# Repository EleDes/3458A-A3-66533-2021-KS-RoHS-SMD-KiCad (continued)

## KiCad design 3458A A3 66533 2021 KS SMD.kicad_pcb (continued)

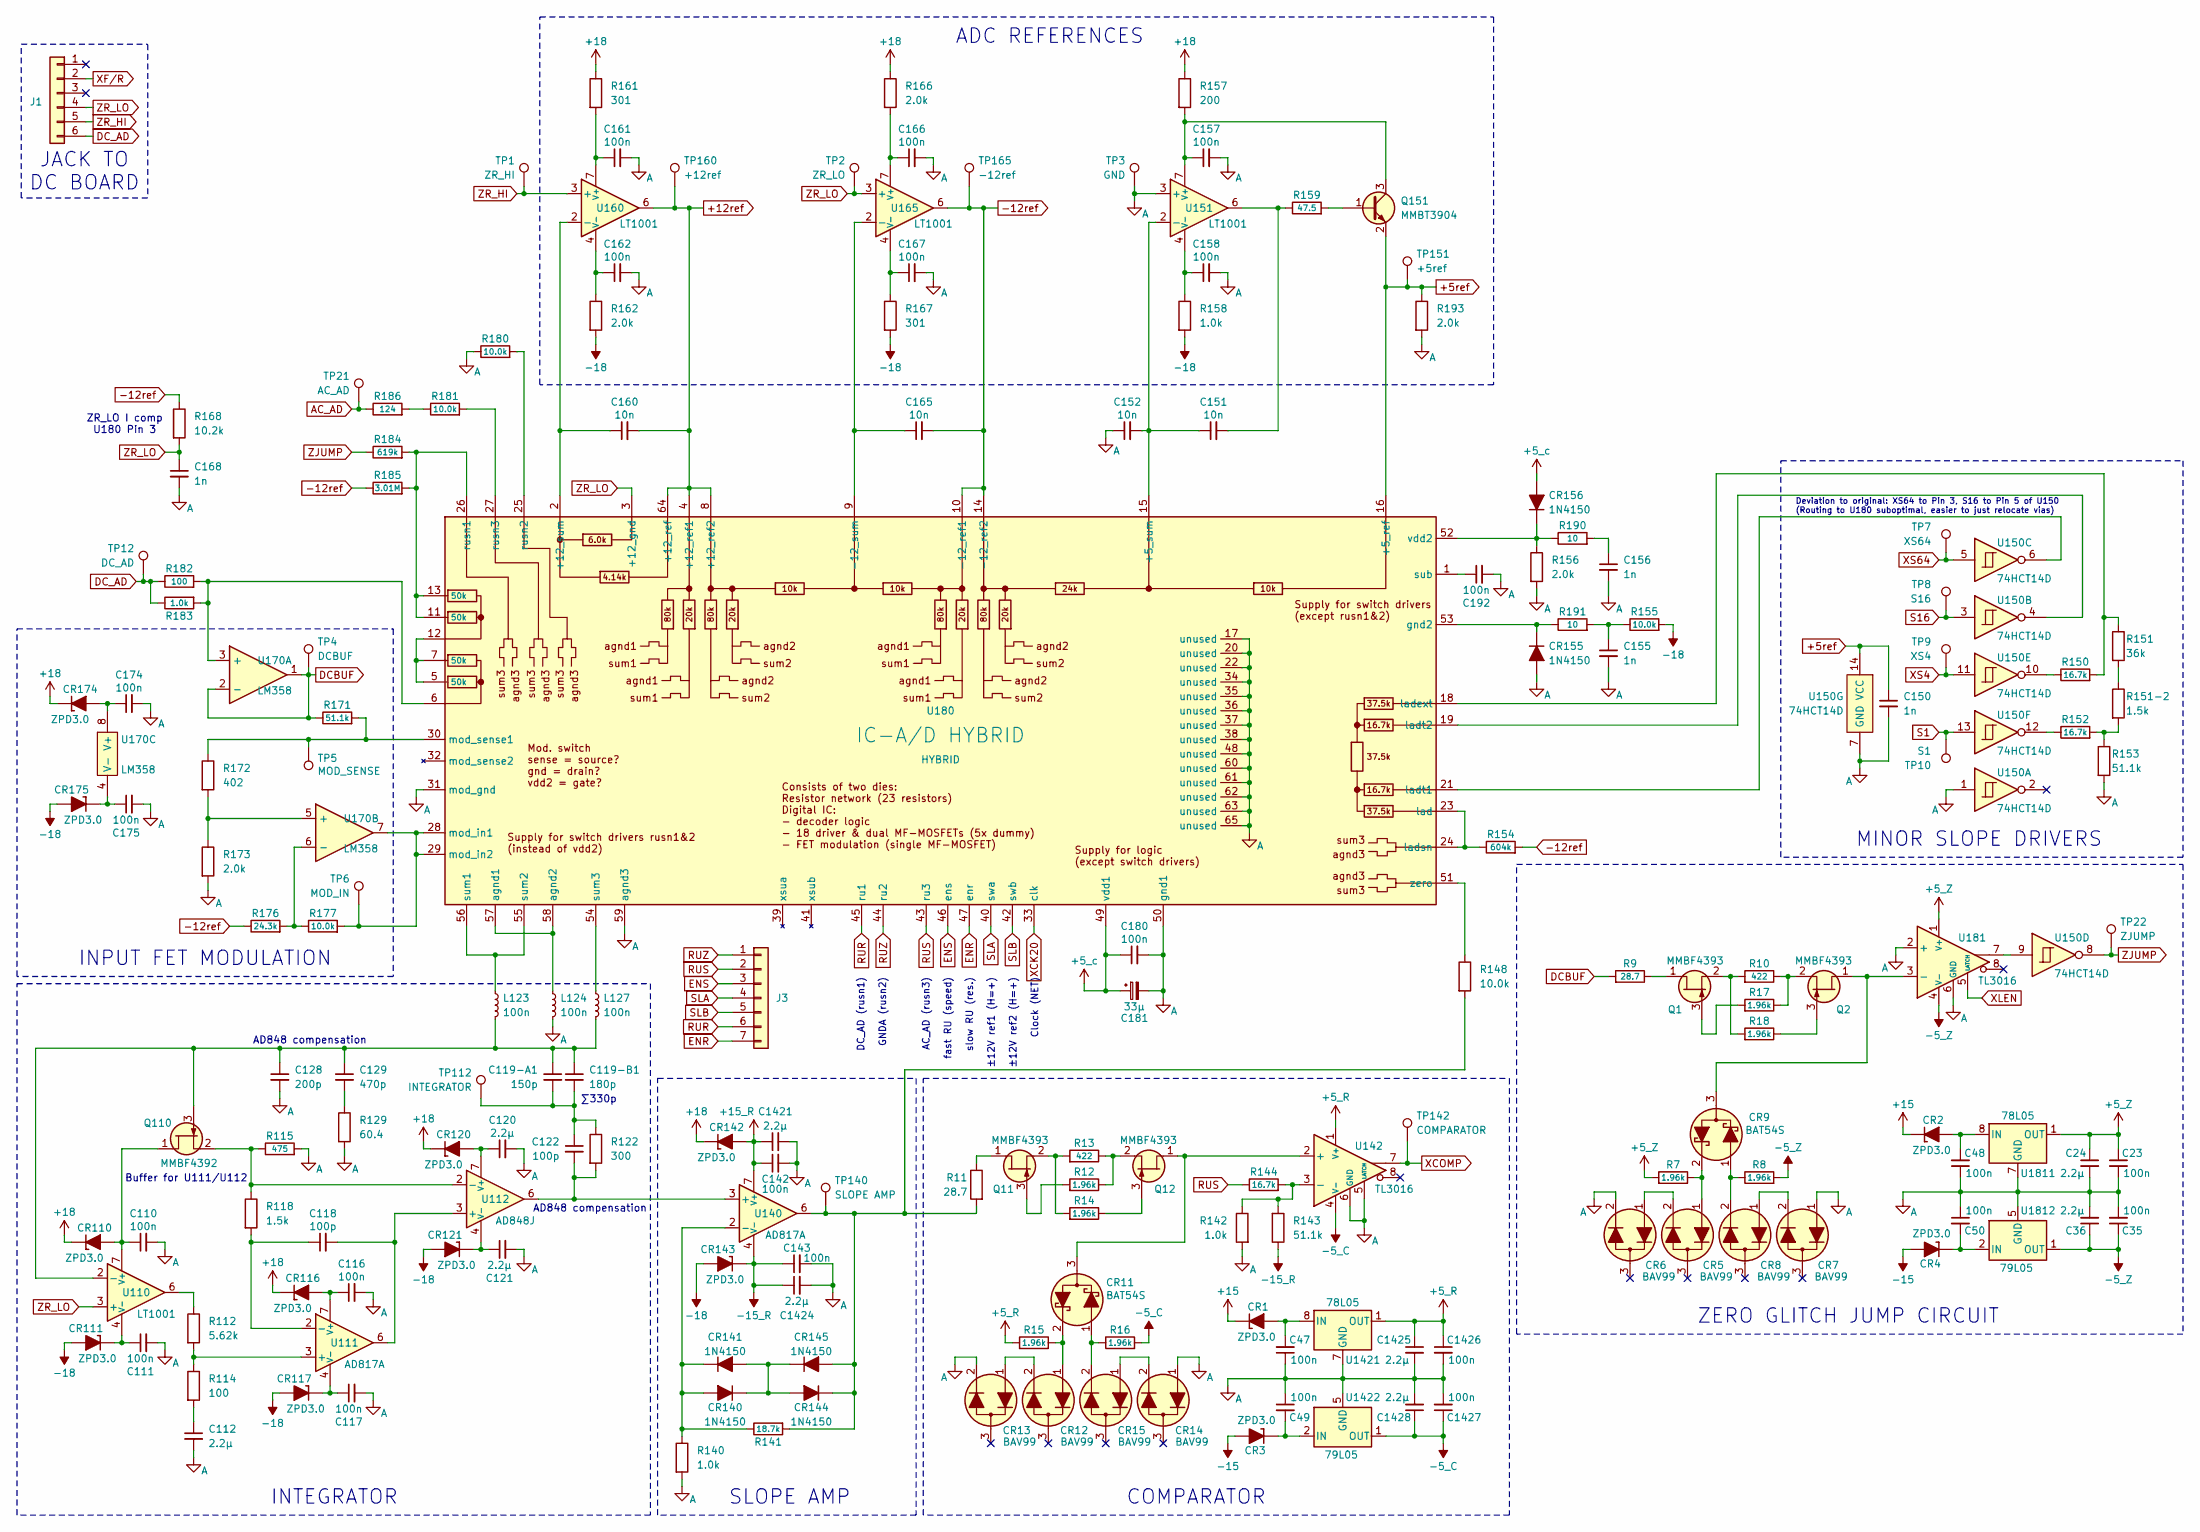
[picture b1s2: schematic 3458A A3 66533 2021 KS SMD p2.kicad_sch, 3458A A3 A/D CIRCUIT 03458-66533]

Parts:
C23, C35, C47, C48, C49, C50, C110, C111, C116, C117, C142, C143, C157, C158, C161, C162, C166, C167, C174, C175, C180, C192, C1426, C1427: 100n; C_0603_1608Metric
C24, C36, C112, C120, C121, C1421, C1424, C1425, C1428: 2.2µ; C_0805_2012Metric
C118, C122: 100p; C_0805_2012Metric
C119-A1: 150p; C_0805_2012Metric
C119-B1: 180p; C_0805_2012Metric
C128: 200p; C_0603_1608Metric
C129: 470p; C_0603_1608Metric
C150, C155, C156, C168: 1n; C_0603_1608Metric
C151, C152, C160, C165: 10n; C_0805_2012Metric
C181: 33µ; CP_EIA-3528-21_Kemet-B
CR1, CR2, CR3, CR4, CR110, CR111, CR116, CR117, CR120, CR121, CR142, CR143, CR174, CR175: ZPD3.0; D_SOD-123; Mfr. Part Number MMSZ5225B
CR5, CR6, CR7, CR8, CR12, CR13, CR14, CR15: BAV99; SOT-23W; Mfr. Part Number BAV99
CR9, CR11: BAT54S; SOT-23W; Mfr. Part Number BAT54S
CR140, CR141, CR144, CR145, CR155, CR156: 1N4150; D_SOD-123; Mfr. Part Number 1N4150W
J1: Conn_01x06; CONN_SDA-41815_06_BE_H_MOL; Mfr. Part Number 09-48-3064
J3: Conn_01x07; PinHeader_1x07_P2.54mm_Vertical
L123, L124, L127: 100n; L_0805_2012Metric
Q1, Q2, Q11, Q12: MMBF4393; SOT-23W; Mfr. Part Number MMBF4393
Q110: MMBF4392; SOT-23W; Mfr. Part Number MMBF4392
Q151: MMBT3904; SOT-23W; Mfr. Part Number MMBT3904
R7, R8, R12, R14, R15, R16, R17, R18: 1.96k; R_1206_3216Metric
R9, R11: 28.7; R_1206_3216Metric
R10, R13: 422; R_1206_3216Metric
R112: 5.62k; R_1206_3216Metric
R114, R182: 100; R_1206_3216Metric
R115: 475; R_1206_3216Metric
R118, R151-2: 1.5k; R_1206_3216Metric
R122: 300; R_1206_3216Metric
R129: 60.4; R_1206_3216Metric
R140, R142, R158, R183: 1.0k; R_1206_3216Metric
R141: 18.7k; R_1206_3216Metric
R143, R153, R171: 51.1k; R_1206_3216Metric
R144, R150, R152: 16.7k; R_1206_3216Metric
R148, R155, R177, R180: 10.0k; R_1206_3216Metric
R151: 36k; R_1206_3216Metric
R154: 604k; R_1206_3216Metric
R156, R162, R166, R173, R193: 2.0k; R_1206_3216Metric
R157: 200; R_1206_3216Metric
R159: 47.5; R_1206_3216Metric
R161, R167: 301; R_1206_3216Metric
R168: 10.2k; R_1206_3216Metric
R172: 402; R_1206_3216Metric
R176: 24.3k; R_1206_3216Metric
R181: 10.0k; R_1206_3216Metric; Mfr. Part Number TNPU120610K0BZ
R184: 619k; R_1206_3216Metric
R185: 3.01M; R_1206_3216Metric
R186: 124; R_1206_3216Metric
R190, R191: 10; R_1206_3216Metric
TP1: ZR_HI; TestPoint_THTPad_2.0x2.0mm_Drill1.0mm; Mfr. Part Number 16-06-0034
TP2: ZR_LO; TestPoint_THTPad_2.0x2.0mm_Drill1.0mm; Mfr. Part Number 16-06-0034
TP3: GND; TestPoint_THTPad_2.0x2.0mm_Drill1.0mm; Mfr. Part Number 16-06-0034
TP4: DCBUF; TestPoint_THTPad_2.0x2.0mm_Drill1.0mm; Mfr. Part Number 16-06-0034
TP5: MOD_SENSE; TestPoint_THTPad_2.0x2.0mm_Drill1.0mm; Mfr. Part Number 16-06-0034
TP6: MOD_IN; TestPoint_THTPad_2.0x2.0mm_Drill1.0mm; Mfr. Part Number 16-06-0034
TP7: XS64; TestPoint_THTPad_2.0x2.0mm_Drill1.0mm; Mfr. Part Number 16-06-0034
TP8: S16; TestPoint_THTPad_2.0x2.0mm_Drill1.0mm; Mfr. Part Number 16-06-0034
TP9: XS4; TestPoint_THTPad_2.0x2.0mm_Drill1.0mm; Mfr. Part Number 16-06-0034
TP10: S1; TestPoint_THTPad_2.0x2.0mm_Drill1.0mm; Mfr. Part Number 16-06-0034
TP12: DC_AD; TestPoint_THTPad_2.0x2.0mm_Drill1.0mm; Mfr. Part Number 16-06-0034
TP21: AC_AD; TestPoint_THTPad_2.0x2.0mm_Drill1.0mm; Mfr. Part Number 16-06-0034
TP22: ZJUMP; TestPoint_THTPad_2.0x2.0mm_Drill1.0mm; Mfr. Part Number 16-06-0034
TP112: INTEGRATOR; TestPoint_THTPad_2.0x2.0mm_Drill1.0mm; Mfr. Part Number 16-06-0034
TP140: SLOPE AMP; TestPoint_THTPad_2.0x2.0mm_Drill1.0mm; Mfr. Part Number 16-06-0034
TP142: COMPARATOR; TestPoint_THTPad_2.0x2.0mm_Drill1.0mm; Mfr. Part Number 16-06-0034
TP151: +5ref; TestPoint_THTPad_2.0x2.0mm_Drill1.0mm; Mfr. Part Number 16-06-0034
TP160: +12ref; TestPoint_THTPad_2.0x2.0mm_Drill1.0mm; Mfr. Part Number 16-06-0034
TP165: -12ref; TestPoint_THTPad_2.0x2.0mm_Drill1.0mm; Mfr. Part Number 16-06-0034
U110, U151, U160, U165: LT1001; SOIC-8_3.9x4.9mm_P1.27mm; Mfr. Part Number LT1001CS8
U111, U140: AD817A; SOIC-8_3.9x4.9mm_P1.27mm; Mfr. Part Number AD817AR
U112: AD848J; SOIC-8_3.9x4.9mm_P1.27mm; Mfr. Part Number AD848JR
U142, U181: TL3016; SOIC-8_3.9x4.9mm_P1.27mm; Mfr. Part Number TL3016
U150: 74HCT14D; SOIC-14_3.9x8.7mm_P1.27mm; Mfr. Part Number 74HCT14D
U170: LM358; SOIC-8_3.9x4.9mm_P1.27mm; Mfr. Part Number LM358
U180: HYBRID; U180_PGA-65; Mfr. Part Number 1SJ8-0108
U1421, U1811: 78L05; SOIC-8_3.9x4.9mm_P1.27mm; Mfr. Part Number MC78L05A
U1422, U1812: 79L05; SOIC-8_3.9x4.9mm_P1.27mm; Mfr. Part Number 79L05A

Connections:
+5_R: C1425.1, C1426.1, R15.2, U142.1 (V+), U1421.1 (OUT); also elsewhere on the board
+5_Z: C23.1, C24.1, R7.2, U181.1 (V+), U1811.1 (OUT); also elsewhere on the board
+5_c: C180.1, C181.1, CR156.2 (A), U180.49 (vdd1); also elsewhere on the board
+5ref: C150.1, Q151.2 (E), R193.1, TP151.1, U150.14 (VCC), U180.16 (+5_ref); also elsewhere on the board
+12ref: C160.2, TP160.1, U160.6, U180.4 (+12_ref1), U180.8 (+12_ref2), U180.64 (+12_ref); also elsewhere on the board
+15: CR1.1 (K), CR2.1 (K); also elsewhere on the board
+15_R: C142.1, C1421.1, CR142.2 (A), U140.7 (V+)
+18: CR110.1 (K), CR116.1 (K), CR120.1 (K), CR142.1 (K), CR174.1 (K), R157.1, R161.1, R166.1; also elsewhere on the board
-5_C: C1427.1, C1428.1, R16.2, U142.4 (V-), U1422.1 (OUT); also elsewhere on the board
-5_Z: C35.1, C36.1, R8.2, U181.4 (V-), U1812.1 (OUT); also elsewhere on the board
-12ref: C165.2, R154.2, R168.1, R176.1, R185.1, TP165.1, U165.6, U180.10 (-12_ref1), U180.14 (-12_ref2); also elsewhere on the board
-15: CR3.2 (A), CR4.2 (A); also elsewhere on the board
-15_R: C143.1, C1424.1, CR143.1 (K), R143.1, U140.4 (V-)
-18: CR111.2 (A), CR117.2 (A), CR121.2 (A), CR143.2 (A), CR175.2 (A), R155.2, R158.2, R162.2, R167.2; also elsewhere on the board
AC_AD: R186.1, TP21.1; also elsewhere on the board
DCBUF: R9.2, R171.1, TP4.1, U170.1, U170.2 (-)
DC_AD: J1.6, R182.1, R183.1, TP12.1
ENR: J3.7, U180.47 (enr); also elsewhere on the board
ENS: J3.3, U180.46 (ens); also elsewhere on the board
unnamed: C112.1, R114.2
unnamed: C119-A1.2, C119-B1.2, C122.1, R122.1, TP112.1
unnamed: C129.2, R129.1
unnamed: C151.2, R159.1, U151.6
unnamed: C155.1, R155.1, R191.2
unnamed: C156.1, R190.2
unnamed: C47.2, CR1.2 (A), U1421.8 (IN)
unnamed: C48.2, CR2.2 (A), U1811.8 (IN)
unnamed: C49.2, CR3.1 (K), U1422.2 (IN), U1422.3 (IN), U1422.6 (IN), U1422.7 (IN)
unnamed: C50.2, CR4.1 (K), U1812.2 (IN), U1812.3 (IN), U1812.6 (IN), U1812.7 (IN)
unnamed: CR5.1 (A), CR9.2 (K), R7.1
unnamed: CR5.2 (K), CR6.1 (A)
unnamed: CR7.2 (K), CR8.1 (A)
unnamed: CR8.2 (K), CR9.1 (A), R8.1
unnamed: CR9.3 (C), Q2.1 (D), U181.3 (-)
unnamed: CR11.1 (A), CR15.2 (K), R16.1
unnamed: CR11.3 (C), Q12.1 (D), U142.2 (+)
unnamed: CR11.2 (K), CR12.1 (A), R15.1
unnamed: CR12.2 (K), CR13.1 (A)
unnamed: CR14.2 (K), CR15.1 (A)
unnamed: C110.1, CR110.2 (A), Q110.1 (D), U110.7 (V+)
unnamed: C111.1, CR111.1 (K), U110.4 (V-)
unnamed: C116.1, CR116.2 (A), U111.7 (V+)
unnamed: C117.1, CR117.1 (K), U111.4 (V-)
unnamed: C120.1, CR120.2 (A), U112.7 (V+)
unnamed: C121.1, CR121.1 (K), U112.4 (V-)
unnamed: CR140.2 (A), CR141.1 (K), R140.1, R141.1, U140.2 (-)
unnamed: CR140.1 (K), CR141.2 (A), CR144.2 (A), CR145.1 (K)
unnamed: CR144.1 (K), CR145.2 (A), R11.2, R141.2, R148.2, TP140.1, U140.6
unnamed: CR155.1 (K), R191.1, U180.53 (gnd2)
unnamed: CR156.1 (K), R156.1, R190.1, U180.52 (vdd2)
unnamed 129: C174.1, CR174.2 (A), U170.8 (V+); also elsewhere on the board
unnamed 130: C175.1, CR175.1 (K), U170.4 (V-); also elsewhere on the board
unnamed: Q1.1 (D), R9.1
unnamed: Q1.3 (G), R17.2
unnamed: Q1.2 (S), R10.2, R18.2
unnamed: Q2.3 (G), R18.1
unnamed: Q2.2 (S), R10.1, R17.1
unnamed: Q11.1 (D), R11.1
unnamed: Q11.3 (G), R12.2
unnamed: Q11.2 (S), R13.2, R14.2
unnamed: Q12.3 (G), R14.1
unnamed: Q12.2 (S), R12.1, R13.1
unnamed: C119-A1.1, C119-B1.1, C128.1, C129.1, L123.2, L127.2, Q110.3 (G), U110.2 (-)
unnamed: Q110.2 (S), R115.1, R118.1, U112.2 (-)
unnamed: Q151.1 (B), R159.2
unnamed: C157.1, Q151.3 (C), R157.2, U151.7 (V+)
unnamed: R112.1, U110.6
unnamed: R150.1, U150.10
unnamed: R151.2, R151-2.1
unnamed: R151-2.2, R152.2, R153.1
unnamed: R152.1, U150.12
unnamed: R181.1, R186.2
unnamed: R112.2, R114.1, U111.3 (+)
unnamed: C118.1, R118.2, U111.2 (-)
unnamed: C118.2, U111.6, U112.3 (+)
unnamed: C122.2, R122.2, U112.6, U140.3 (+)
unnamed: R142.1, R143.2, R144.2, U142.3 (-)
unnamed: U150.9, U181.7
unnamed: C151.1, C152.2, U151.2 (-), U180.15 (+5_sum)
unnamed: C158.1, R158.1, U151.4 (V-)
unnamed: C160.1, U160.2 (-), U180.2 (+12_sum)
unnamed: C161.1, R161.2, U160.7 (V+)
unnamed: C162.1, R162.1, U160.4 (V-)
unnamed: C165.1, U165.2 (-), U180.9 (-12_sum)
unnamed: C166.1, R166.2, U165.7 (V+)
unnamed: C167.1, R167.1, U165.4 (V-)
unnamed: R182.2, R183.2, U170.3 (+), U180.6
unnamed: R172.2, R173.1, U170.5 (+)
unnamed: R176.2, R177.1, U170.6 (-)
unnamed: U180.5 (50k), U180.7 (50k), U180.12
unnamed: L124.1, U180.57 (agnd1), U180.58 (agnd2)
unnamed: R154.1, U180.23 (lad), U180.24 (ladsn)
unnamed: R150.2, R151.1, U180.18 (ladext)
unnamed: U150.6, U180.21 (ladt1)
unnamed: U150.4, U180.19 (ladt2)
unnamed: R177.2, TP6.1, U170.7, U180.28 (mod_in1), U180.29 (mod_in2)
unnamed: R171.2, R172.1, TP5.1, U180.30 (mod_sense1)
unnamed: R184.2, R185.2, U180.11 (50k), U180.13 (50k), U180.26 (rusn1)
unnamed: R180.2, U180.25 (rusn2)
unnamed: R181.2, U180.27 (rusn3)
unnamed: C192.1, U180.1 (sub)
unnamed: L123.1, U180.55 (sum2), U180.56 (sum1)
unnamed: L127.1, U180.54 (sum3)
unnamed: R148.1, U180.51 (zero)
PS_SENSE: C23.2, C24.2, C35.2, C36.2, C47.1, C48.1, C49.1, C50.1, C110.2, C111.2, C112.2, C116.2, C117.2, C120.2, C121.2, C128.2, C142.2, C143.2, C150.2, C152.1, C155.2, C156.2, C157.2, C158.2, C161.2, C162.2, C166.2, C167.2, C168.2, C174.2, C175.2, C180.2, C181.2, C192.2, C1421.2, C1424.2, C1425.2, C1426.2, C1427.2, C1428.2, CR6.2 (K), CR7.1 (A), CR13.2 (K), CR14.1 (A), CR155.2 (A), L124.2, R115.2, R129.2, R140.2, R142.2, R153.2, R156.2, R173.2, R180.1, R193.2, TP3.1, U142.5 (LATCH), U142.6 (GND), U150.1, U150.7 (GND), U151.3 (+), U180.17 (unused), U180.20 (unused), U180.22 (unused), U180.31 (mod_gnd), U180.34 (unused), U180.35 (unused), U180.36 (unused), U180.37 (unused), U180.38 (unused), U180.48 (unused), U180.50 (gnd1), U180.59 (agnd3), U180.60 (unused), U180.61 (unused), U180.62 (unused), U180.63 (unused), U180.65 (unused), U181.2 (+), U181.6 (GND), U1421.2 (GND), U1421.3 (GND), U1421.6 (GND), U1421.7 (GND), U1422.5 (GND), U1811.2 (GND), U1811.3 (GND), U1811.6 (GND), U1811.7 (GND), U1812.5 (GND); also elsewhere on the board
RUR: J3.6, U180.45 (ru1); also elsewhere on the board
RUS: J3.2, R144.1, U180.43 (ru3); also elsewhere on the board
RUZ: J3.1, U180.44 (ru2); also elsewhere on the board
S1: TP10.1, U150.13; also elsewhere on the board
S16: TP8.1, U150.3; also elsewhere on the board
SLA: J3.4, U180.40 (swa); also elsewhere on the board
SLB: J3.5, U180.42 (swb); also elsewhere on the board
XCK20: U180.33 (clk); also elsewhere on the board
XCOMP: TP142.1, U142.7; also elsewhere on the board
XF/R: J1.2; also elsewhere on the board
XLEN: U181.5 (LATCH); also elsewhere on the board
XS4: TP9.1, U150.11; also elsewhere on the board
XS64: TP7.1, U150.5; also elsewhere on the board
ZJUMP: R184.1, TP22.1, U150.8
ZR_HI: J1.5, TP1.1, U160.3 (+)
ZR_LO: C168.1, J1.4, R168.2, TP2.1, U110.3 (+), U165.3 (+), U180.3 (+12_gnd)

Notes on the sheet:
ZR_LO I comp U180 Pin 3
JACK TO DC BOARD
INPUT FET MODULATION
AD848 compensation
ZERO GLITCH JUMP CIRCUIT
MINOR SLOPE DRIVERS
Deviation to original: XS64 to Pin 3, S16 to Pin 5 of U150 (Routing to U180 suboptimal, easier to just relocate vias)
ADC REFERENCES
INTEGRATOR
Buffer for U111/U112
∑330p
SLOPE AMP
DC_AD (rusn1) GNDA (rusn2) AC_AD (rusn3) fast RU (speed) slow RU (res.) ±12V ref1 (H=+) ±12V ref2 (H=+) Clock (NET)
COMPARATOR

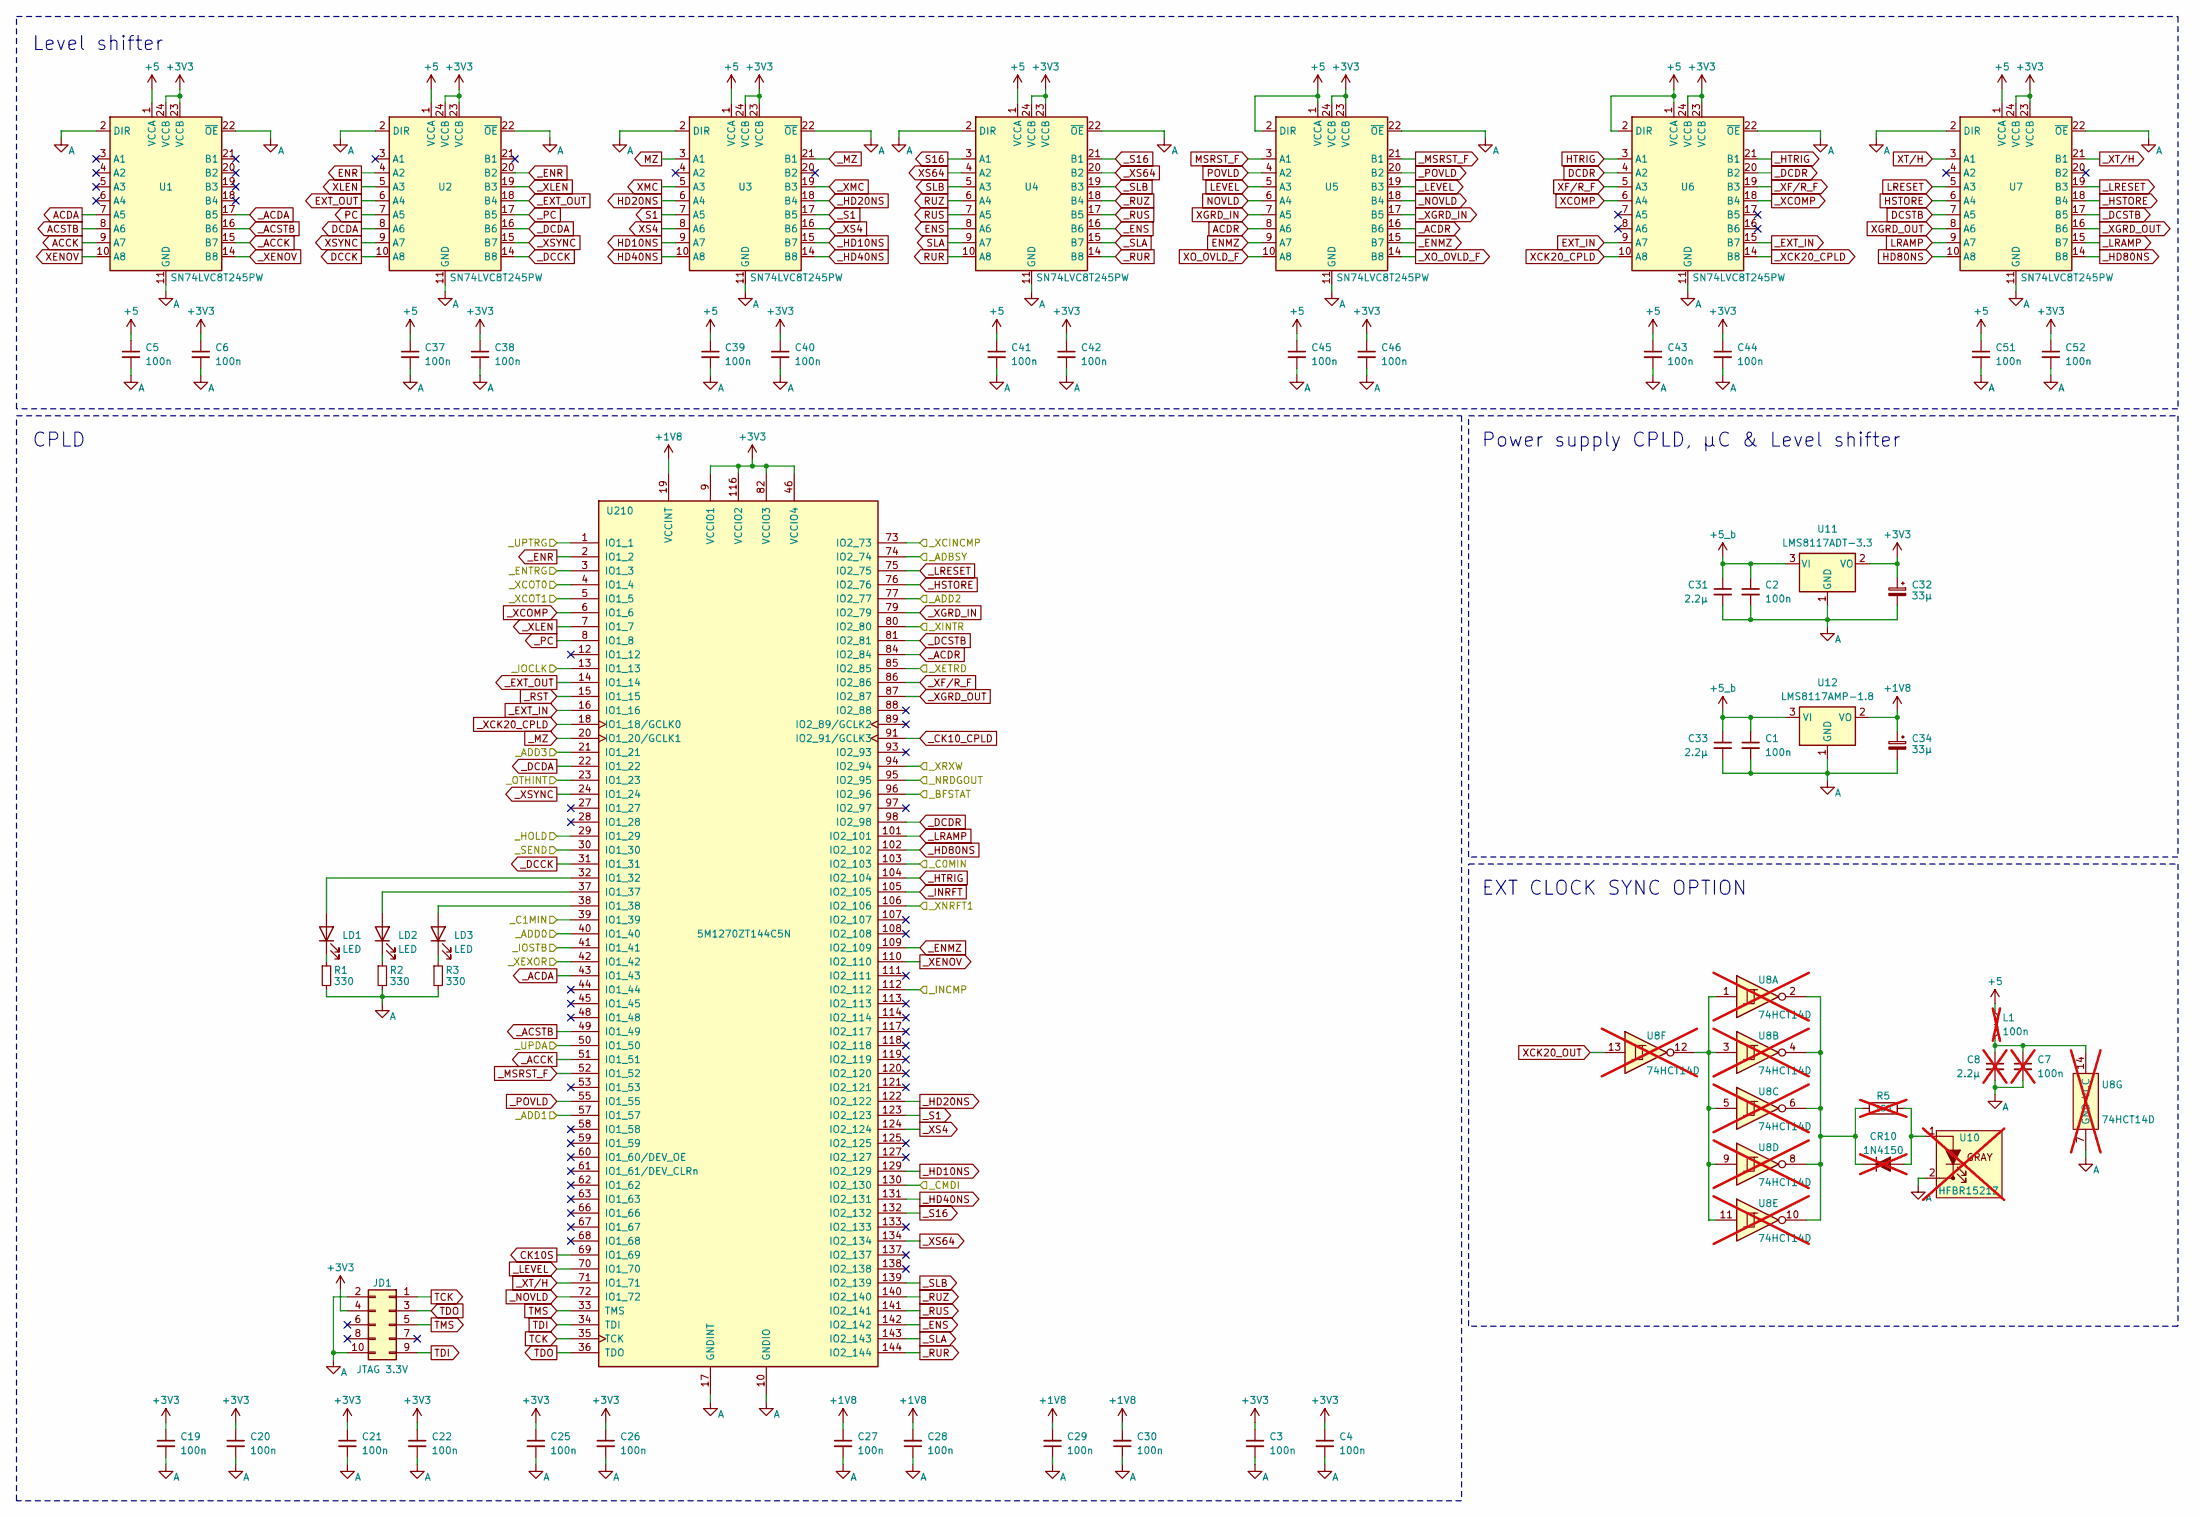
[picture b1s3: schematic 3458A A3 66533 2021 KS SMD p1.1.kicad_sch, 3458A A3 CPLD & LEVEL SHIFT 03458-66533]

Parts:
C1, C2, C3, C4, C5, C6, C19, C20, C21, C22, C25, C26, C28, C29, C30, C37, C38, C39, C40, C41, C42, C43, C44, C46, C51, C52: 100n; C_0603_1608Metric
C7: 100n; C_0603_1608Metric; not fitted
C8: 2.2µ; C_0805_2012Metric; not fitted
C27, C45: 100n; C_0805_2012Metric
C31, C33: 2.2µ; C_0805_2012Metric
C32, C34: 33µ; CP_EIA-3528-21_Kemet-B
CR10: 1N4150; D_SOD-123; Mfr. Part Number 1N4150W; not fitted
JD1: JTAG 3.3V; PinHeader_2x05_P2.54mm_Vertical
L1: 100n; L_0603_1608Metric; not fitted
LD1, LD2, LD3: LED; LED_0603_1608Metric
R1, R2, R3: 330; R_0603_1608Metric
R5: 150; R_1206_3216Metric; not fitted
U1, U2, U3, U4, U5, U6, U7: SN74LVC8T245PW; TSSOP-24_4.4x7.8mm_P0.65mm; Mfr. Part Number SN74LVC8T245PW
U8: 74HCT14D; SOIC-14_3.9x8.7mm_P1.27mm; Mfr. Part Number 74HCT14D; not fitted
U10: HFBR1521Z; HFBR-1521Z Fiber Optic; Mfr. Part Number HFBR1521Z; not fitted
U11: LMS8117ADT-3.3; TO-252-2; Mfr. Part Number LMS8117ADT-3.3
U12: LMS8117AMP-1.8; SOT-223-3_TabPin2; Mfr. Part Number LMS8117AMP-1.8
U210: 5M1270ZT144C5N; LQFP-144_20x20mm_P0.5mm; Mfr. Part Number 5M1270ZT144C5N

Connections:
+1V8: C27.1, C28.2, C29.2, C30.2, C34.1, U12.2 (VO), U210.19 (VCCINT), U210.56 (VCCINT), U210.90 (VCCINT), U210.126 (VCCINT); also elsewhere on the board
+3V3: C3.1, C4.1, C6.1, C19.1, C20.1, C21.1, C22.1, C25.1, C26.1, C32.1, C38.1, C40.1, C42.1, C44.1, C46.1, C52.1, JD1.4, U1.23 (VCCB), U1.24 (VCCB), U2.23 (VCCB), U2.24 (VCCB), U3.23 (VCCB), U3.24 (VCCB), U4.23 (VCCB), U4.24 (VCCB), U5.23 (VCCB), U5.24 (VCCB), U6.23 (VCCB), U6.24 (VCCB), U7.23 (VCCB), U7.24 (VCCB), U11.2 (VO), U210.9 (VCCIO1), U210.25 (VCCIO1), U210.46 (VCCIO4), U210.64 (VCCIO4), U210.82 (VCCIO3), U210.100 (VCCIO3), U210.116 (VCCIO2), U210.136 (VCCIO2); also elsewhere on the board
+5: C5.1, C37.1, C39.1, C41.1, C43.1, C45.1, C51.1, L1.1, U1.1 (VCCA), U2.1 (VCCA), U3.1 (VCCA), U4.1 (VCCA), U5.1 (VCCA), U5.2 (DIR), U6.1 (VCCA), U6.2 (DIR), U7.1 (VCCA); also elsewhere on the board
+5_b: C1.1, C2.1, C31.1, C33.1, U11.3 (VI), U12.3 (VI); also elsewhere on the board
/A3 IN-GRD CTL & INTERPOLATOR/CPLD & LEVEL SHIFT (Seite 2)/_ADBSY: U210.74 (IO2_74); also elsewhere on the board
/A3 IN-GRD CTL & INTERPOLATOR/CPLD & LEVEL SHIFT (Seite 2)/_ADD0: U210.40 (IO1_40); also elsewhere on the board
/A3 IN-GRD CTL & INTERPOLATOR/CPLD & LEVEL SHIFT (Seite 2)/_ADD1: U210.57 (IO1_57); also elsewhere on the board
/A3 IN-GRD CTL & INTERPOLATOR/CPLD & LEVEL SHIFT (Seite 2)/_ADD2: U210.77 (IO2_77); also elsewhere on the board
/A3 IN-GRD CTL & INTERPOLATOR/CPLD & LEVEL SHIFT (Seite 2)/_ADD3: U210.21 (IO1_21); also elsewhere on the board
/A3 IN-GRD CTL & INTERPOLATOR/CPLD & LEVEL SHIFT (Seite 2)/_BFSTAT: U210.96 (IO2_96); also elsewhere on the board
/A3 IN-GRD CTL & INTERPOLATOR/CPLD & LEVEL SHIFT (Seite 2)/_C0MIN: U210.103 (IO2_103); also elsewhere on the board
/A3 IN-GRD CTL & INTERPOLATOR/CPLD & LEVEL SHIFT (Seite 2)/_C1MIN: U210.39 (IO1_39); also elsewhere on the board
/A3 IN-GRD CTL & INTERPOLATOR/CPLD & LEVEL SHIFT (Seite 2)/_CMDI: U210.130 (IO2_130); also elsewhere on the board
/A3 IN-GRD CTL & INTERPOLATOR/CPLD & LEVEL SHIFT (Seite 2)/_ENTRG: U210.3 (IO1_3); also elsewhere on the board
/A3 IN-GRD CTL & INTERPOLATOR/CPLD & LEVEL SHIFT (Seite 2)/_HOLD: U210.29 (IO1_29); also elsewhere on the board
/A3 IN-GRD CTL & INTERPOLATOR/CPLD & LEVEL SHIFT (Seite 2)/_INCMP: U210.73 (IO2_73), U210.112 (IO2_112); also elsewhere on the board
/A3 IN-GRD CTL & INTERPOLATOR/CPLD & LEVEL SHIFT (Seite 2)/_IOCLK: U210.13 (IO1_13); also elsewhere on the board
/A3 IN-GRD CTL & INTERPOLATOR/CPLD & LEVEL SHIFT (Seite 2)/_IOSTB: U210.41 (IO1_41); also elsewhere on the board
/A3 IN-GRD CTL & INTERPOLATOR/CPLD & LEVEL SHIFT (Seite 2)/_NRDGOUT: U210.95 (IO2_95); also elsewhere on the board
/A3 IN-GRD CTL & INTERPOLATOR/CPLD & LEVEL SHIFT (Seite 2)/_OTHINT: U210.23 (IO1_23); also elsewhere on the board
/A3 IN-GRD CTL & INTERPOLATOR/CPLD & LEVEL SHIFT (Seite 2)/_SEND: U210.30 (IO1_30); also elsewhere on the board
/A3 IN-GRD CTL & INTERPOLATOR/CPLD & LEVEL SHIFT (Seite 2)/_UPDA: U210.50 (IO1_50); also elsewhere on the board
/A3 IN-GRD CTL & INTERPOLATOR/CPLD & LEVEL SHIFT (Seite 2)/_UPTRG: U210.1 (IO1_1); also elsewhere on the board
/A3 IN-GRD CTL & INTERPOLATOR/CPLD & LEVEL SHIFT (Seite 2)/_XETRD: U210.85 (IO2_85); also elsewhere on the board
/A3 IN-GRD CTL & INTERPOLATOR/CPLD & LEVEL SHIFT (Seite 2)/_XEXOR: U210.42 (IO1_42); also elsewhere on the board
/A3 IN-GRD CTL & INTERPOLATOR/CPLD & LEVEL SHIFT (Seite 2)/_XINTR: U210.80 (IO2_80); also elsewhere on the board
/A3 IN-GRD CTL & INTERPOLATOR/CPLD & LEVEL SHIFT (Seite 2)/_XRXW: U210.94 (IO2_94); also elsewhere on the board
ACCK: U1.9 (A7); also elsewhere on the board
ACDA: U1.7 (A5); also elsewhere on the board
ACDR: U5.8 (A6); also elsewhere on the board
ACSTB: U1.8 (A6); also elsewhere on the board
CK10S: U210.69 (IO1_69); also elsewhere on the board
DCCK: U2.10 (A8); also elsewhere on the board
DCDA: U2.8 (A6); also elsewhere on the board
DCDR: U6.4 (A2); also elsewhere on the board
DCSTB: U7.7 (A5); also elsewhere on the board
ENMZ: U5.9 (A7); also elsewhere on the board
ENR: U2.4 (A2); also elsewhere on the board
ENS: U4.8 (A6); also elsewhere on the board
EXT_IN: U6.9 (A7); also elsewhere on the board
EXT_OUT: U2.6 (A4); also elsewhere on the board
HD10NS: U3.9 (A7); also elsewhere on the board
HD20NS: U3.6 (A4); also elsewhere on the board
HD40NS: U3.10 (A8); also elsewhere on the board
HD80NS: U7.10 (A8); also elsewhere on the board
HSTORE: U7.6 (A4); also elsewhere on the board
HTRIG: U6.3 (A1); also elsewhere on the board
LEVEL: U5.5 (A3); also elsewhere on the board
LRAMP: U7.9 (A7); also elsewhere on the board
LRESET: U7.5 (A3); also elsewhere on the board
MISO: U210.5 (IO1_5); also elsewhere on the board
MOSI: U210.4 (IO1_4); also elsewhere on the board
MSRST_F: U5.3 (A1); also elsewhere on the board
MZ: U3.3 (A1); also elsewhere on the board
NOVLD: U5.6 (A4); also elsewhere on the board
unnamed: CR10.2 (A), R5.2, U10.1 (A)
unnamed: CR10.1 (K), R5.1, U8.2, U8.4, U8.6, U8.8, U8.10
unnamed: LD1.2 (A), U210.32 (IO1_32)
unnamed: LD1.1 (K), R1.1
unnamed: LD2.2 (A), U210.37 (IO1_37)
unnamed: LD2.1 (K), R2.1
unnamed: LD3.2 (A), U210.38 (IO1_38)
unnamed: LD3.1 (K), R3.1
unnamed: U8.1, U8.3, U8.5, U8.9, U8.11, U8.12
unnamed: C7.1, C8.1, L1.2, U8.14 (VCC)
PC: U2.7 (A5); also elsewhere on the board
POVLD: U5.4 (A2); also elsewhere on the board
PS_SENSE: C1.2, C2.2, C3.2, C4.2, C5.2, C6.2, C7.2, C8.2, C19.2, C20.2, C21.2, C22.2, C25.2, C26.2, C27.2, C28.1, C29.1, C30.1, C31.2, C32.2, C33.2, C34.2, C37.2, C38.2, C39.2, C40.2, C41.2, C42.2, C43.2, C44.2, C45.2, C46.2, C51.2, C52.2, JD1.2, JD1.10, R1.2, R2.2, R3.2, U1.2 (DIR), U1.11 (GND), U1.12 (GND), U1.13 (GND), U1.22 (~OE), U2.2 (DIR), U2.11 (GND), U2.12 (GND), U2.13 (GND), U2.22 (~OE), U3.2 (DIR), U3.11 (GND), U3.12 (GND), U3.13 (GND), U3.22 (~OE), U4.2 (DIR), U4.11 (GND), U4.12 (GND), U4.13 (GND), U4.22 (~OE), U5.11 (GND), U5.12 (GND), U5.13 (GND), U5.22 (~OE), U6.11 (GND), U6.12 (GND), U6.13 (GND), U6.22 (~OE), U7.2 (DIR), U7.11 (GND), U7.12 (GND), U7.13 (GND), U7.22 (~OE), U8.7 (GND), U10.2 (K), U11.1 (GND), U12.1 (GND), U210.10 (GNDIO), U210.11 (GNDIO), U210.17 (GNDINT), U210.26 (GNDIO), U210.47 (GNDIO), U210.54 (GNDINT), U210.65 (GNDIO), U210.78 (GNDIO), U210.83 (GNDIO), U210.92 (GNDINT), U210.99 (GNDIO), U210.115 (GNDIO), U210.128 (GNDINT), U210.135 (GNDIO); also elsewhere on the board
RUR: U4.10 (A8); also elsewhere on the board
RUS: U4.7 (A5); also elsewhere on the board
RUZ: U4.6 (A4); also elsewhere on the board
S1: U3.7 (A5); also elsewhere on the board
S16: U4.3 (A1); also elsewhere on the board
SCK: U210.106 (IO2_106); also elsewhere on the board
SLA: U4.9 (A7); also elsewhere on the board
SLB: U4.5 (A3); also elsewhere on the board
TCK: JD1.1, U210.35 (TCK)
TDI: JD1.9, U210.34 (TDI)
TDO: JD1.3, U210.36 (TDO)
TMS: JD1.5, U210.33 (TMS)
XCK20_CPLD: U6.10 (A8); also elsewhere on the board
XCK20_OUT: U8.13; also elsewhere on the board
XCOMP: U6.6 (A4); also elsewhere on the board
XENOV: U1.10 (A8); also elsewhere on the board
XF/R_F: U6.5 (A3); also elsewhere on the board
XGRD_IN: U5.7 (A5); also elsewhere on the board
XGRD_OUT: U7.8 (A6); also elsewhere on the board
XLEN: U2.5 (A3); also elsewhere on the board
XMC: U3.5 (A3); also elsewhere on the board
XO_OVLD_F: U5.10 (A8); also elsewhere on the board
XS4: U3.8 (A6); also elsewhere on the board
XS64: U4.4 (A2); also elsewhere on the board
XSYNC: U2.9 (A7); also elsewhere on the board
XT/H: U7.3 (A1); also elsewhere on the board
_ACCK: U1.15 (B7), U210.51 (IO1_51)
_ACDA: U1.17 (B5), U210.43 (IO1_43)
_ACDR: U5.16 (B6), U210.84 (IO2_84)
_ACSTB: U1.16 (B6), U210.49 (IO1_49)
_CK10_CPLD: U210.91 (IO2_91/GCLK3); also elsewhere on the board
_DCCK: U2.14 (B8), U210.31 (IO1_31)
_DCDA: U2.16 (B6), U210.22 (IO1_22)
_DCDR: U6.20 (B2), U210.98 (IO2_98)
_DCSTB: U7.17 (B5), U210.81 (IO2_81)
_ENMZ: U5.15 (B7), U210.109 (IO2_109)
_ENR: U2.20 (B2), U210.2 (IO1_2)
_ENS: U4.16 (B6), U210.142 (IO2_142)
_EXT_IN: U6.15 (B7), U210.16 (IO1_16)
_EXT_OUT: U2.18 (B4), U210.14 (IO1_14)
_HD10NS: U3.15 (B7), U210.129 (IO2_129)
_HD20NS: U3.18 (B4), U210.122 (IO2_122)
_HD40NS: U3.14 (B8), U210.131 (IO2_131)
_HD80NS: U7.14 (B8), U210.102 (IO2_102)
_HSTORE: U7.18 (B4), U210.76 (IO2_76)
_HTRIG: U6.21 (B1), U210.104 (IO2_104)
_INRFT: U210.105 (IO2_105); also elsewhere on the board
_LEVEL: U5.19 (B3), U210.70 (IO1_70); also elsewhere on the board
_LRAMP: U7.15 (B7), U210.101 (IO2_101)
_LRESET: U7.19 (B3), U210.75 (IO2_75)
_MSRST_F: U5.21 (B1), U210.52 (IO1_52)
_MZ: U3.21 (B1), U210.20 (IO1_20/GCLK1); also elsewhere on the board
_NOVLD: U5.18 (B4), U210.72 (IO1_72)
_PC: U2.17 (B5), U210.8 (IO1_8); also elsewhere on the board
_POVLD: U5.20 (B2), U210.55 (IO1_55)
_RST: U210.15 (IO1_15); also elsewhere on the board
_RUR: U4.14 (B8), U210.144 (IO2_144)
_RUS: U4.17 (B5), U210.141 (IO2_141)
_RUZ: U4.18 (B4), U210.140 (IO2_140)
_S1: U3.17 (B5), U210.123 (IO2_123)
_S16: U4.21 (B1), U210.132 (IO2_132)
_SLA: U4.15 (B7), U210.143 (IO2_143)
_SLB: U4.19 (B3), U210.139 (IO2_139)
_XCK20_CPLD: U6.14 (B8), U210.18 (IO1_18/GCLK0)
_XCOMP: U6.18 (B4), U210.6 (IO1_6)
_XENOV: U1.14 (B8), U210.110 (IO2_110)
_XF/R_F: U6.19 (B3), U210.86 (IO2_86)
_XGRD_IN: U5.17 (B5), U210.79 (IO2_79)
_XGRD_OUT: U7.16 (B6), U210.87 (IO2_87)
_XLEN: U2.19 (B3), U210.7 (IO1_7)
_XMC: U3.19 (B3); also elsewhere on the board
_XO_OVLD_F: U5.14 (B8); also elsewhere on the board
_XS4: U3.16 (B6), U210.124 (IO2_124)
_XS64: U4.20 (B2), U210.134 (IO2_134)
_XSYNC: U2.15 (B7), U210.24 (IO1_24)
_XT/H: U7.21 (B1), U210.71 (IO1_71)

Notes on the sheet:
Level shifter
CPLD
Power supply CPLD, µC & Level shifter
EXT CLOCK SYNC OPTION
